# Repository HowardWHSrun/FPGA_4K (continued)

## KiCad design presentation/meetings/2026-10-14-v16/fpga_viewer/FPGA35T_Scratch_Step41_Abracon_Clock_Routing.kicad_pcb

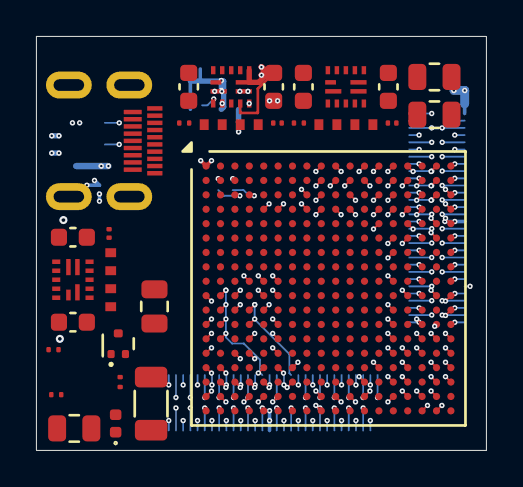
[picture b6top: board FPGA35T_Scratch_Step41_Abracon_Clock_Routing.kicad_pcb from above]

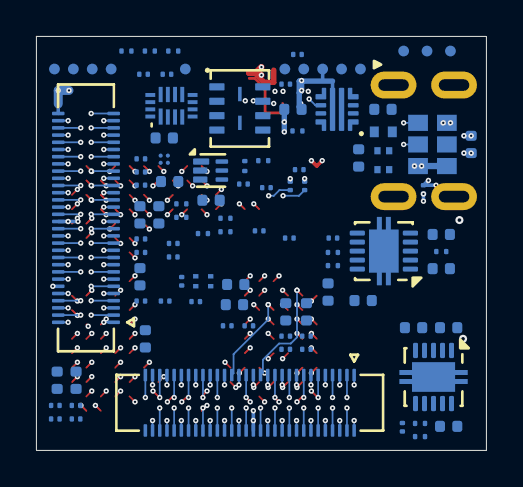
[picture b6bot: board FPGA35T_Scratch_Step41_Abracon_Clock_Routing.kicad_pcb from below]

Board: 8 copper layers, 25.0 x 23.0 mm, 135 parts (103 on the bottom side), 180 nets.

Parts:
C1, C2, C12, C13, C21, C22: 22uF; C_0603_1608Metric
C3, C14, C23: 22pF; C_0201_GRM03_Murata_0p22Gap
C4: 100uF; C_1206_3216Metric
C5, C6, C16, C17, C24, C25, C30, C31, C36, C37, C43, C44, C45, C47, C48, C49, C51, C54: 4.7uF; C_0402_1005Metric
C7, C8, C9, C11, C18, C19, C20, C26, C27, C28, C29, C32, C33, C34, C35, C38, C39, C40, C41, C57, C58: 470nF; C_0201_GRM03_Murata_0p22Gap
C10, C15, C42, C59: 47uF; C_0805_2012Metric
C46, C50: 10nF; C_0201_GRM03_Murata_0p22Gap
C52, C53, C55, C56, C60, C78, C79, C80, C83: 100nF; C_0201_GRM03_Murata_0p22Gap
C61, C82, C84: 1uF; C_0402_1005Metric
C62, C63: 220nF; C_0201_GRM03_Murata_0p22Gap
C75: 1uF / 25V; C_0402_1005Metric
C76: 1uF / 10V; C_0402_1005Metric
C77: 3.3nF / 25V; C_0201_GRM03_Murata_0p22Gap
C81: 10uF; C_0402_1005Metric
D1: SML-P11UTT86R / RED; ROHM_SML_P11_1006
J1, J2: DF40C-60DS-0.4V(51); Hirose_DF40C-60DS-0.4V_2x30_P0.4mm
J3: Micro-HDMI 467651001; Molex_MicroHDMI_46765_1xxx
L1, L2: MPZ0603S121HT000; TDK_MPZ0603S121HT000_0201_Land_0p25x0p30_Gap0p30
Q1: RYM002N05T2CL; ROHM_VMT3_SOT723
R1, R4: 200k; R_0402_TE_CPF_Reflow_0p50Gap
R2: 301k; R_0402_TE_CPF_Reflow_0p50Gap
R3, R6, R11, R14, R38: 4.99k; R_0201_ERA1A_Panasonic_0p30Gap
R5, R8: 100k; R_0402_TE_CPF_Reflow_0p50Gap
R7: 150k; R_0402_TE_CPF_Reflow_0p50Gap
R9, R12, R40: 10k; R_0201_ERA1A_Panasonic_0p30Gap
R10: 1.24k; R_0201_ERA1A_Panasonic_0p30Gap
R13: 2.49k; R_0201_ERA1A_Panasonic_0p30Gap
R16: 100R; R_0201_ERA1A_Panasonic_0p30Gap
R17, R18, R19, R20, R21, R22: 4.7k; R_0201_ERA1A_Panasonic_0p30Gap
R25: 470R; R_0201_ERA1A_Panasonic_0p30Gap
R27: 1k; R_0201_ERA1A_Panasonic_0p30Gap
R34: 174k; R_0402_TE_CPF_Reflow_0p50Gap
R35: 24.9k; R_0201_Yageo_RT_RE_Reflow_1p00Span
R36: 100k; R_0201_Yageo_RT_RE_Reflow_1p00Span
R37: 6.49k; R_0201_ERA1A_Panasonic_0p30Gap
R39: 1.5k; R_0201_ERA1A_Panasonic_0p30Gap
TP1, TP2, TP3, TP4, TP5, TP6, TP7, TP8, TP9, TP10, TP11, TP12, TP13: 0.6mm COPPER; TestPoint_Pad_D0.6mm_Edge_NoPaste
U1: XC7A35T-2CSG325I; Xilinx_CSG325
U2, U3, U4: MPM3834CGPA; MPM3834C_ECLGA14_2.5x2.5mm
U5, U6: TPS74801DRCRM3; VSON-10-1EP_3x3mm_P0.5mm_EP1.65x2.4mm
U7: IS25WP032D-JTLE; ISSI_USON8_4x3mm_T
U8: NVT4858HKZ; NXP_NVT4858HK_XQFN16_SOT1161-2_1.8x2.6mm_P0.4mm
U10: TPS259470ARPWR; TI_RPW0010A_HotRod_2x2mm
U11: TPS22916B / fast + QOD; TI_TPS22916_YFP0004_DSBGA4_0.78x0.78mm_P0.4mm
U12: TPS389018 / timed INIT hold; TI_DSE0006A_WSON6_1p5x1p5_P0p5_Manufacturer
Y1: AX3DCF1-125.0000T3 / 125 MHz; Abracon_AX3_3225_6pin

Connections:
/ASIC1_CLK32MHz_Out: J1.9, U1.P14 (L12P_T1_MRCC)
/ASIC1_DATA1: J1.1, U1.J14 (L5P_T0_D06)
/ASIC1_DATA2: J1.2, U1.V16 (L18P_T2_A12_D28)
/ASIC1_DATA3: J1.3, U1.V17 (L18N_T2_A11_D27)
/ASIC1_DATA4: J1.4, U1.K15 (L5N_T0_D07)
/ASIC1_DATA5: J1.5, U1.K17 (L4P_T0_D04)
/ASIC1_DATA6: J1.6, U1.K18 (L3N_T0_DQS_EMCCLK)
/ASIC1_DATA7: J1.7, U1.L14 (IO0)
/ASIC1_DATA8: J1.8, U1.L18 (L4N_T0_D05)
/ASIC1_READ: J1.10, U1.M14 (L8P_T1_D11)
/ASIC1_SYNC: J1.11, U1.M16 (L7P_T1_D09)
/ASIC2_CLK32MHz_Out: J1.20, U1.T14 (L13P_T2_MRCC)
/ASIC2_DATA1: J1.12, U1.M17 (L7N_T1_D10)
/ASIC2_DATA2: J1.13, U1.N14 (L8N_T1_D12)
/ASIC2_DATA3: J1.14, U1.N16 (L9P_T1_DQS)
/ASIC2_DATA4: J1.15, U1.N17 (L9N_T1_DQS_D13)
/ASIC2_DATA5: J1.16, U1.N18 (L10P_T1_D14)
/ASIC2_DATA6: J1.17, U1.P16 (L11N_T1_SRCC)
/ASIC2_DATA7: J1.18, U1.P18 (L10N_T1_D15)
/ASIC2_DATA8: J1.19, U1.R13 (L19P_T3_A10_D26)
/ASIC2_READ: J1.21, U1.R15 (L12N_T1_MRCC)
/ASIC2_SYNC: J1.22, U1.R17 (L14N_T2_SRCC)
/ASIC3_CLK32MHz_Out: J1.32, U1.P15 (L11P_T1_SRCC)
/ASIC3_DATA1: J1.23, U1.R18 (L15P_T2_DQS_RDWR_B)
/ASIC3_DATA2: J1.24, U1.T12 (L22P_T3_A05_D21)
/ASIC3_DATA3: J1.25, U1.T15 (L13N_T2_MRCC)
/ASIC3_DATA4: J1.26, U1.T17 (L16P_T2_CSI_B)
/ASIC3_DATA5: J1.27, U1.T18 (L15N_T2_DQS_DOUT_CSO_B)
/ASIC3_DATA6: J1.28, U1.U9 (L24P_T3_A01_D17)
/ASIC3_DATA7: J1.29, U1.U10 (IO25)
/ASIC3_DATA8: J1.31, U1.U11 (L23P_T3_A03_D19)
/ASIC3_READ: J1.33, U1.U12 (L22N_T3_A04_D20)
/ASIC3_SYNC: J1.34, U1.U14 (L20P_T3_A08_D24)
/ASIC4_CLK32MHz_Out: J1.43, U1.E13 (L12P_T1_MRCC)
/ASIC4_DATA1: J1.35, U1.A9 (L3N_T0_DQS_AD1N)
/ASIC4_DATA2: J1.36, U1.A10 (L5N_T0_AD9N)
/ASIC4_DATA3: J1.37, U1.A12 (L7N_T1_AD2N)
/ASIC4_DATA4: J1.38, U1.A13 (L8P_T1_AD10P)
/ASIC4_DATA5: J1.39, U1.A14 (L8N_T1_AD10N)
/ASIC4_DATA6: J1.40, U1.A15 (L10N_T1_AD11N)
/ASIC4_DATA7: J1.41, U1.A17 (L15N_T2_DQS_ADV_B)
/ASIC4_DATA8: J1.42, U1.B9 (L3P_T0_DQS_AD1P)
/ASIC4_READ: J1.44, U1.B10 (L5P_T0_AD9P)
/ASIC4_SYNC: J1.45, U1.B11 (L4N_T0)
/ASIC5_CLK32MHz_Out: J2.9, U1.E15 (L13P_T2_MRCC)
/ASIC5_DATA1: J2.1, U1.B12 (L7P_T1_AD2P)
/ASIC5_DATA2: J2.2, U1.B14 (L10P_T1_AD11P)
/ASIC5_DATA3: J2.3, U1.B15 (L9N_T1_DQS_AD3N)
/ASIC5_DATA4: J2.4, U1.B16 (L15P_T2_DQS)
/ASIC5_DATA5: J2.5, U1.B17 (L16N_T2_A27)
/ASIC5_DATA6: J2.6, U1.C8 (L1N_T0_AD0N)
/ASIC5_DATA7: J2.7, U1.C9 (L2N_T0_AD8N)
/ASIC5_DATA8: J2.8, U1.C11 (L4P_T0)
/ASIC5_READ: J2.10, U1.C13 (L11N_T1_SRCC)
/ASIC5_SYNC: J2.11, U1.C14 (L9P_T1_DQS_AD3P)
/ASIC6_CLK32MHz_Out: J2.20, U1.D13 (L11P_T1_SRCC)
/ASIC6_DATA1: J2.12, U1.C16 (L16P_T2_A28)
/ASIC6_DATA2: J2.13, U1.C17 (L18P_T2_A24)
/ASIC6_DATA3: J2.14, U1.C18 (L18N_T2_A23)
/ASIC6_DATA4: J2.15, U1.D8 (L1P_T0_AD0P)
/ASIC6_DATA5: J2.16, U1.D9 (L2P_T0_AD8P)
/ASIC6_DATA6: J2.17, U1.D10 (IO0)
/ASIC6_DATA7: J2.18, U1.D11 (L6P_T0)
/ASIC6_DATA8: J2.19, U1.D14 (L12N_T1_MRCC)
/ASIC6_READ: J2.21, U1.D15 (L13N_T2_MRCC)
/ASIC6_SYNC: J2.22, U1.D16 (L14N_T2_SRCC)
/ASIC7_CLK32MHz_Out: J2.32, U1.P4 (L12P_T1_MRCC)
/ASIC7_DATA1: J2.23, U1.J4 (L2N_T0)
/ASIC7_DATA2: J2.24, U1.J5 (L2P_T0)
/ASIC7_DATA3: J2.25, U1.J6 (IO0)
/ASIC7_DATA4: J2.26, U1.K1 (L3N_T0_DQS)
/ASIC7_DATA5: J2.27, U1.K2 (L3P_T0_DQS)
/ASIC7_DATA6: J2.28, U1.K3 (L4P_T0)
/ASIC7_DATA7: J2.29, U1.K5 (L1N_T0)
/ASIC7_DATA8: J2.31, U1.K6 (L1P_T0)
/ASIC7_READ: J2.33, U1.L2 (L4N_T0)
/ASIC7_SYNC: J2.34, U1.L3 (L5N_T0)
/ASIC8_CLK32MHz_Out: J2.43, U1.R2 (L13P_T2_MRCC)
/ASIC8_DATA1: J2.35, U1.L4 (L5P_T0)
/ASIC8_DATA2: J2.36, U1.L5 (L6P_T0)
/ASIC8_DATA3: J2.37, U1.M1 (L7N_T1)
/ASIC8_DATA4: J2.38, U1.M2 (L7P_T1)
/ASIC8_DATA5: J2.39, U1.M4 (L10P_T1)
/ASIC8_DATA6: J2.40, U1.M6 (L8P_T1)
/ASIC8_DATA7: J2.41, U1.N1 (L9P_T1_DQS)
/ASIC8_DATA8: J2.42, U1.N2 (L11N_T1_SRCC)
/ASIC8_READ: J2.44, U1.N4 (L10N_T1)
/ASIC8_SYNC: J2.45, U1.N6 (L8N_T1)
/CHIP_RESET_SHARED: J1.56, U1.T3 (L17N_T2)
/FE_RESET_SHARED: J1.57, U1.T4 (L17P_T2)
/IMP_TST_SHARED: J1.58, U1.D18 (L17N_T2_A25)
/LED_USER_A: D1.2 (A), R39.2
/LED_USER_K: D1.1 (K), Q1.3 (D)
/NONSTIM_BOARD1_SPI_DL: J1.54, U1.T5 (L21N_T3_DQS)
/NONSTIM_BOARD1_SPI_DR: J1.55, U1.E17 (L17P_T2_A26)
/NONSTIM_BOARD2_SPI_DL: J2.54, U1.T7 (L22N_T3)
/NONSTIM_BOARD2_SPI_DR: J2.55, U1.E18 (L24N_T3_RS0)
/OSC125_N: C79.1, Y1.5 (OUTN)
/OSC125_P: C78.1, Y1.4 (OUTP)
/STIM_CHIP1_SPI_DL: J1.50, U1.U2 (L15P_T2_DQS)
/STIM_CHIP1_SPI_DR: J1.51, U1.U15 (L17P_T2_A14_D30)
/STIM_CHIP2_SPI_DL: J1.52, U1.F15 (L21N_T3_DQS_A18)
/STIM_CHIP2_SPI_DR: J1.53, U1.U4 (L18P_T2)
/STIM_CHIP3_SPI_DL: J2.50, U1.U16 (L17N_T2_A13_D29)
/STIM_CHIP3_SPI_DR: J2.51, U1.F17 (L24P_T3_RS1)
/STIM_CHIP4_SPI_DL: J2.52, U1.U5 (L20N_T3)
/STIM_CHIP4_SPI_DR: J2.53, U1.U17 (L16N_T2_A15_D31)
BOARD1_CLK: J1.46, U1.P1 (L9N_T1_DQS)
BOARD1_SPI_CLK: J1.48, U1.P3 (L12N_T1_MRCC)
BOARD2_CLK: J1.47, U1.P6 (L19P_T3)
BOARD2_SPI_CLK: J1.49, U1.R1 (L13N_T2_MRCC)
BOARD3_CLK: J2.46, U1.R5 (L21P_T3_DQS)
BOARD3_SPI_CLK: J2.48, U1.R6 (IO25)
BOARD4_CLK: J2.47, U1.R7 (L22P_T3)
BOARD4_SPI_CLK: J2.49, U1.T2 (L14N_T2_SRCC)
BOOT_RAILS_PG_3V3: R9.2, TP10.1 (PAD_1), U4.11 (PG), U6.3 (PG), U11.B2 (ON), U12.3 (MR_/_PG_ready)
CABLE_TARGET_SENSE: J3.1 (SENSE), R27.2
FLASH_1V8_SW: C60.1, C62.1, R22.1, TP9.1 (PAD_1), U7.8 (VCC_1.8_V), U8.14, U11.A1 (VOUT)
FLASH_CS_N_1V8: R22.2, U7.1 (CE#), U8.13
FLASH_DQ0_1V8: U7.5 (SI_/_DQ0), U8.10
FLASH_DQ1_1V8: U7.2 (SO_/_DQ1), U8.9
FLASH_DQ2_1V8: U7.3 (WP#_/_DQ2), U8.12
FLASH_DQ3_1V8: U7.7 (HOLD#_/_DQ3), U8.11
FLASH_SCK_1V8: U7.6 (SCK), U8.8
FPGA_DONE: R38.2, TP12.1 (PAD_1), U1.F12 (DONE_0)
FPGA_INIT_B: R18.2, TP11.1 (PAD_1), U1.T10 (INIT_B_0), U12.6 (RESET_/_hold_INIT)
FPGA_JTAG_TCK: J3.17 (TCK), U1.F8 (TCK_0)
FPGA_JTAG_TDI: J3.15 (TDI), U1.T9 (TDI_0)
FPGA_JTAG_TDO: J3.18 (TDO), U1.T8 (TDO_0)
FPGA_JTAG_TMS: J3.2 (TMS), U1.R8 (TMS_0)
FPGA_LED_USER: Q1.1 (G), R40.1, U1.U7 (L23P_T3)
FPGA_PROGRAM_B: R17.2, U1.P10 (PROGRAM_B_0)
FPGA_PUDC_B: R25.2, U1.J18 (L3P_T0_DQS_PUDC_B)
FPGA_QSPI_CCLK: U1.E8 (CCLK_0), U8.5
FPGA_QSPI_CS_N: R19.2, U1.L15 (L6P_T0_FCS_B), U8.16
FPGA_QSPI_DQ0: U1.K16 (L1P_T0_D00_MOSI), U8.3
FPGA_QSPI_DQ1: U1.L17 (L1N_T0_D01_DIN), U8.4
FPGA_QSPI_DQ2: R20.2, U1.J15 (L2P_T0_D02), U8.1
FPGA_QSPI_DQ3: R21.2, U1.J16 (L2N_T0_D03), U8.2
GND: C1.2, C2.2, C4.2, C5.2, C6.2, C7.2, C8.2, C9.2, C10.2, C11.2, C12.2, C13.2, C15.2, C16.2, C17.2, C18.2, C19.2, C20.2, C21.2, C22.2, C24.2, C25.2, C26.2, C27.2, C28.2, C29.2, C30.2, C31.2, C32.2, C33.2, C34.2, C35.2, C36.2, C37.2, C38.2, C39.2, C40.2, C41.2, C42.2, C43.1, C44.2, C45.2, C46.2, C47.1, C48.2, C49.2, C50.2, C51.2, C52.2, C53.2, C54.2, C55.2, C56.2, C58.2, C59.2, C60.2, C61.2, C62.2, C63.2, C75.2, C76.2, C77.2, C80.2, C81.2, C82.2, C83.2, C84.2, J1.30, J2.30, J3.4 (GND), J3.7 (GND), J3.10 (GND), J3.13 (GND), J3.16 (GND), J3.SH (SHIELD), L2.1, Q1.2 (S), R2.2, R5.2, R8.2, R11.2, R14.2, R36.2, R37.2, R40.2, TP1.1 (PAD_1), TP13.1 (PAD_1), U1.A1 (GND_[75_balls]), U1.A5 (GND), U1.A7 (GND), U1.A8 (GND), U1.A11 (GND), U1.A18 (GND), U1.B3 (GND), U1.B7 (GND), U1.B8 (GND), U1.B18 (GND), U1.C2 (GND), U1.C3 (MGTPRXN2_216), U1.C4 (MGTPRXP2_216), U1.C6 (GND), U1.C7 (GND), U1.C15 (GND), U1.D3 (GND), U1.D4 (GND), U1.D7 (GND), U1.D12 (GND), U1.E2 (GND), U1.E3 (MGTPRXN0_216), U1.E4 (MGTPRXP0_216), U1.E6 (GND), U1.E7 (GND), U1.E9 (GND), U1.E11 (VCCBATT_0), U1.E12 (CFGBVS_0), U1.F4 (GND), U1.F6 (GND), U1.F10 (GND), U1.F13 (M2_0), U1.F16 (GND), U1.G1 (GND), U1.G3 (MGTPRXN3_216), U1.G4 (MGTPRXP3_216), U1.G5 (GND), U1.G6 (GND), U1.G7 (GND), U1.G9 (GND), U1.G11 (GND), U1.G13 (GND), U1.H3 (GND), U1.H4 (GND), U1.H5 (GND), U1.H6 (GND), U1.H8 (GND), U1.H10 (GND), U1.H12 (GND), U1.J1 (GND), U1.J2 (GND), U1.J3 (GND), U1.J7 (GND), U1.J11 (GND), U1.J13 (GND), U1.J17 (GND), U1.K4 (GND), U1.K8 (GND), U1.K12 (GND), U1.K14 (GND), U1.L1 (GND), U1.L7 (GND), U1.L11 (GND), U1.L13 (GND), U1.M8 (GND), U1.M9 (DXN_0), U1.M10 (DXP_0), U1.M12 (GND), U1.M18 (GND), U1.N5 (GND), U1.N7 (GND), U1.N9 (GND), U1.N11 (GND), U1.N13 (GND), U1.N15 (GND), U1.P2 (GND), U1.P8 (GND), U1.P12 (GND), U1.R9 (GND), U1.R11 (M1_0), U1.T6 (GND), U1.T16 (GND), U1.U3 (GND), U1.U13 (GND), U1.V1 (GND), U1.V10 (GND), U1.V18 (GND), U2.2 (PGND), U2.4 (AGND), U2.7 (PGND), U2.8 (PGND), U3.2 (PGND), U3.4 (AGND), U3.7 (PGND), U3.8 (PGND), U4.2 (PGND), U4.4 (AGND), U4.7 (PGND), U4.8 (PGND), U5.6 (GND), U5.11 (GND_EP), U6.6 (GND), U6.11 (GND_EP), U7.4 (GND_/_optional_tabs), U8.7, U10.8 (GND), U11.B1 (GND), U12.2 (GND), Y1.3 (GND)
GNDADC_XADC: C57.2, L2.2, U1.J9 (GNDADC_0), U1.K9 (VREFN_0), U1.K10 (VP_0), U1.L9 (VN_0), U1.L10 (VREFP_0)
GTP_REFCLK0_N: C79.2, U1.D5 (MGTREFCLK0N_216)
GTP_REFCLK0_P: C78.2, U1.D6 (MGTREFCLK0P_216)
GTP_RX1_N: J3.14 (RX1_N), U1.A3 (MGTPRXN1_216)
GTP_RX1_P: J3.12 (RX1_P), U1.A4 (MGTPRXP1_216)
GTP_TX0_N: J3.5 (TX0_N), U1.H1 (MGTPTXN0_216)
GTP_TX0_P: J3.3 (TX0_P), U1.H2 (MGTPTXP0_216)
GTP_TX1_N: J3.8 (TX1_N), U1.F1 (MGTPTXN1_216)
GTP_TX1_P: J3.6 (TX1_P), U1.F2 (MGTPTXP1_216)
GTP_TX2_N: J3.11 (TX2_N), U1.D1 (MGTPTXN2_216)
GTP_TX2_P: J3.9 (TX2_P), U1.D2 (MGTPTXP2_216)
HDMI_PWR_RAW: C75.1, J3.19 (3V3_IN), R34.1, TP2.1 (PAD_1), U10.5 (IN)
MGTAVCC_1V0: C45.1, C51.1, C52.1, C53.1, R10.1, TP7.1 (PAD_1), U1.B4 (MGTAVCC), U1.C5 (MGTAVCC), U1.E5 (MGTAVCC), U1.F5 (MGTAVCC), U5.9 (OUT), U5.10 (OUT)
MGTAVTT_1V2: C49.1, C54.1, C55.1, C56.1, R13.1, R16.1, TP8.1 (PAD_1), U1.A2 (MGTAVTT), U1.C1 (MGTAVTT), U1.E1 (MGTAVTT), U1.F3 (MGTAVTT), U1.G2 (MGTAVTT), U6.9 (OUT), U6.10 (OUT)
unnamed: R16.2, U1.A6 (MGTRREF_216)
unnamed: C3.2, R1.2, R2.1, U2.5 (FB)
unnamed: C14.2, R4.2, R5.1, U3.5 (FB)
unnamed: C23.2, R7.2, R8.1, U4.5 (FB)
unnamed: R10.2, R11.1, U5.8 (FB)
unnamed: C46.1, U5.7 (SS)
unnamed: R13.2, R14.1, U6.8 (FB)
unnamed: C50.1, U6.7 (SS)
unnamed: C84.1, U12.5 (CT)
PG_AUX_1V8: R6.2, U3.11 (PG), U4.3 (EN), U5.5 (EN)
PG_CORE_1V0: R3.2, U2.11 (PG), U3.3 (EN)
PG_MGT_1V0: R12.2, U5.3 (PG), U6.5 (EN)
PWR_DVDT: C77.1, U10.7 (dVdt)
PWR_EN_UVLO: R34.2, R35.1, U10.1 (EN/UVLO)
PWR_ILM: R37.1, U10.9 (ILM)
PWR_OVLO: R35.2, R36.1, U10.2 (OVLO)
SPI_LATCH_SHARED: J1.59, U1.U1 (L15N_T2_DQS)
STIM_CHB_SHARED: J2.59, U1.F14 (L22N_T3_A16)
STIM_CLK_SHARED: J2.56, U1.G14 (L22P_T3_A17)
STIM_EN_SHARED: J2.58, U1.U6 (L20P_T3)
STIM_START_SHARED: J2.57, U1.V9 (L24N_T3_A00_D16)
VCCADC_1V8: C57.1, L1.2, U1.J10 (VCCADC_0)
VCCAUX_1V8: C13.1, C14.1, C15.1, C16.1, C17.1, C18.1, C19.1, C20.1, C43.2, C47.2, C58.1, C80.1, C81.1, C82.1, L1.1, R4.1, TP5.1 (PAD_1), U1.G12 (VCCAUX_[5_balls]), U1.H13 (VCCAUX), U1.K13 (VCCAUX), U1.M13 (VCCAUX), U1.P13 (VCCAUX), U3.6 (OUT_S), U3.9 (OUT), U3.10 (OUT), U5.1 (IN), U5.2 (IN), U6.1 (IN), U6.2 (IN), U11.A2 (VIN), U12.1 (SENSE_/_AUX1.8), Y1.1 (OE), Y1.6 (VDD)
VCCINT_1V0: C2.1, C3.1, C4.1, C5.1, C6.1, C7.1, C8.1, C9.1, C10.1, C11.1, R1.1, TP4.1 (PAD_1), U1.F7 (VCCINT_1V0), U1.F9 (VCCINT_1V0), U1.F11 (VCCBRAM/VCCINT_[21_balls]), U1.G8 (VCCINT_1V0), U1.G10 (VCCBRAM_1V0), U1.H7 (VCCINT_1V0), U1.H9 (VCCINT_1V0), U1.H11 (VCCBRAM_1V0), U1.J8 (VCCINT_1V0), U1.J12 (VCCINT_1V0), U1.K7 (VCCINT_1V0), U1.K11 (VCCINT_1V0), U1.L8 (VCCINT_1V0), U1.L12 (VCCINT_1V0), U1.M7 (VCCINT_1V0), U1.M11 (VCCINT_1V0), U1.N8 (VCCINT_1V0), U1.N10 (VCCINT_1V0), U1.N12 (VCCINT_1V0), U1.P9 (VCCINT_1V0), U1.P11 (VCCINT_1V0), U2.6 (OUT_S), U2.9 (OUT), U2.10 (OUT)
VCCO_1V5: C22.1, C23.1, C24.1, C25.1, C26.1, C27.1, C28.1, C29.1, C30.1, C31.1, C32.1, C33.1, C34.1, C35.1, C36.1, C37.1, C38.1, C39.1, C40.1, C41.1, C42.1, C59.1, C61.1, C63.1, R7.1, R17.1, R18.1, R19.1, R20.1, R21.1, R25.1, R27.1, R38.1, TP6.1 (PAD_1), U1.A16 (VCCO), U1.B13 (VCCO), U1.C10 (VCCO), U1.D17 (VCCO), U1.E10 (VCCO_0), U1.E14 (VCCO), U1.G18 (VCCO), U1.H15 (VCCO), U1.L6 (VCCO), U1.L16 (VCCO), U1.M3 (VCCO), U1.P7 (VCCO), U1.P17 (VCCO), U1.R4 (VCCO), U1.R10 (VCCO_0), U1.R12 (M0_0), U1.R14 (VCCO), U1.T1 (VCCO), U1.T11 (VCCO), U1.U8 (VCCO), U1.U18 (VCCO), U1.V5 (VCCO), U1.V15 (VCCO), U4.6 (OUT_S), U4.9 (OUT), U4.10 (OUT), U8.15
VIN_3V3: C1.1, C12.1, C21.1, C44.1, C48.1, C76.1, C83.1, J1.60, R3.1, R6.1, R9.1, R12.1, R39.1, TP3.1 (PAD_1), U2.3 (EN), U2.12 (IN), U2.13 (IN), U2.14 (IN), U3.12 (IN), U3.13 (IN), U3.14 (IN), U4.12 (IN), U4.13 (IN), U4.14 (IN), U5.4 (BIAS), U6.4 (BIAS), U10.6 (OUT), U12.4 (VDD)
